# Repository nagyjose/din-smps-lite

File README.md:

# DIN-Rail Switched-Mode Power Supply Lite (`din-smps-lite`)

> Ultra-compact, cost- and space-optimized offline flyback auxiliary power supply for 35 mm DIN-rail modular enclosures, delivering a regulated +12 V DC rail.

**Project Status:** `Completed / Production Ready` | **EDA Tool:** `Autodesk Eagle 9.x` | **Category:** `Power Electronics / Hardware`

---

## 1. Overview and Purpose

The `din-smps-lite` repository provides an ultra-compact, high-efficiency offline AC/DC switched-mode power supply designed for DIN-rail distribution enclosures and localized automation sub-racks. It serves as a streamlined, space-optimized alternative to the dual-output [din-smps](https://github.com/nagyjose/din-smps) main model.

By focusing on a single high-integrity **+12 V DC** regulated rail and utilizing standing component footprints, this design achieves a minimal PCB footprint while retaining full galvanic isolation (> 3 kV) and mains protection.

### Key Features
- **Galvanic Isolation:** High-voltage isolation exceeding 3 kV via an optocoupler feedback loop and specialized flyback transformer.
- **High Efficiency & Low Standby:** Powered by the **Power Integrations TNY267PN** TinySwitch-II offline switcher with EcoSmart® technology, providing auto-restart, cycle skipping, and thermal shutdown.
- **Input Protection:** AC mains surge suppression via a Metal Oxide Varistor (`VAR1`, 420V AC / 680V clamping) and overcurrent protection via a resettable PTC fuse (`FX1`).
- **Single Regulated +12 V DC Rail:** Regulated by an **STMicroelectronics L7812ABV** linear regulator with bulk electrolytic and ceramic decoupling for noise-free relay, actuator, and bus power.
- **Space-Saving Footprints:** Utilizes vertical/standing component geometries (`_STOJ`) for axial resistors to minimize overall PCB dimensions.
- **Ready for Manufacture:** Complete Autodesk Eagle schematic (`.sch`), 2-layer PCB layout (`.brd`), CAM drill configuration (`DRILEGEND.CFG`), and PDF drawings.

---

## 2. Technical Specifications

| Parameter | Specification (`SMPS-DIN-LITE`) |
| :--- | :--- |
| **Input Voltage Range** | 85 – 265 V AC, 50/60 Hz |
| **Input Connector** | 2-position 5.00 mm screw terminal (`CON1`: Line, Neutral) |
| **Primary Topology** | Discontinuous Conduction Mode (DCM) Flyback Converter |
| **Primary Controller IC** | Power Integrations TNY267PN (DIP-8B) |
| **Flyback Transformer** | Myrra 74080 (designed for TinySwitch-II) |
| **Output Voltage** | **+12 V DC** (Regulated) |
| **Linear Post-Regulator** | STMicroelectronics L7812ABV (TO-220) |
| **Output Rectifier** | 1N5822 (3 A / 40 V Schottky Barrier Rectifier) |
| **Feedback Loop** | Sharp PC817 optocoupler + 15 V Zener diode reference |
| **Input Protection** | Resettable PTC Fuse (`FX1`) + MOV 680 V (`VAR1`, HEL-7D681K) |
| **Output Connector** | 2-position 5.00 mm screw terminal (`CON2`: +12 V, GND) |
| **PCB Form Factor** | Double-sided 1.6 mm FR4, compact DIN-rail layout |

---

## 3. Architecture & Functional Blocks

```mermaid
flowchart TD
    subgraph AC_Input["Mains AC Input Stage"]
        AC["230V AC Mains (L, N)"] --> PROT["Protection<br/>(PTC Fuse FX1 + MOV HEL-7D681K)"]
        PROT --> RECT["Full-Bridge Rectifier<br/>(4x 1N4005)"]
        RECT --> DC_BUS["DC Bus & Filter<br/>(Pi-Filter: 2x 3.3µF / 400V + 2.2mH L1)"]
    end

    subgraph Primary_Flyback["Galvanically Isolated Flyback Converter"]
        DC_BUS --> TR["Flyback Transformer<br/>(Myrra 74080)"]
        DC_BUS --> RCD["RCD Snubber<br/>(1N4005 + 2MΩ / 100kΩ + 2.2nF)"]
        RCD --> TR
        TR <--> TNY["Flyback Switcher IC<br/>(Power Integrations TNY267PN)"]
    end

    subgraph Secondary_Output["Secondary Rectification & Regulation"]
        TR --> SCHOTTKY["Secondary Rectifier<br/>(1N5822 Schottky 3A)"]
        SCHOTTKY --> SEC_FILT["Bulk Filtering<br/>(1000µF + 10µH L2 + 470µF)"]
        SEC_FILT --> REG12["Linear Regulator 12V<br/>(ST L7812ABV)"]
        REG12 --> OUT12["+12V DC Output (CON2)"]
    end

    subgraph Feedback_Loop["Optocoupler Feedback"]
        SEC_FILT --> ZENER["Voltage Reference<br/>(15V Zener D7 + R5 680Ω)"]
        ZENER --> OPTO["Galvanic Optocoupler<br/>(Sharp PC817)"]
        OPTO -.->|Isolated Feedback Current| TNY
    end

    style AC fill:#e1f5fe,stroke:#0288d1,stroke-width:1.5px
    style TNY fill:#fff3e0,stroke:#f57c00,stroke-width:2px
    style TR fill:#ede7f6,stroke:#512da8,stroke-width:2px
    style OUT12 fill:#e8f5e9,stroke:#388e3c,stroke-width:2px
```

### Circuit Operation
1. **Mains Ingress & Rectification:** AC mains enters through 2-pin terminal block `CON1`, protected against short circuits by PTC fuse `FX1` and voltage surges by varistor `VAR1`. A 1N4005 diode bridge (`D1`–`D4`) rectifies the input into a high-voltage DC bus smoothed by a pi-filter (`C1`, `C2` 3.3 µF / 400 V and `L1` 2.2 mH choke).
2. **Flyback Switching (TNY267PN):** The integrated 700 V MOSFET in `IC1` switches the primary winding of transformer `TR1` (Myrra 74080). Drain voltage transients are suppressed by the snubber network (`D5`, `R2`, `R3`, `C4`).
3. **Optocoupler Regulation:** Output voltage is sampled through a 15 V Zener diode (`D7`) driving the infrared LED of optocoupler `IC2` (PC817). The phototransistor modulates the `EN/UV` terminal of the TNY267PN, enabling cycle-skipping regulation.
4. **Secondary Smoothing & Linear Regulation:** High-efficiency rectification is handled by Schottky diode `D6` (1N5822) followed by a CLC smoothing stage (`C8`, `L2`, `C10`). Linear regulator `IC3` (L7812ABV) clamps and stabilizes the final rail at exactly **+12.0 V DC** on `CON2`.

---

## 4. Hardware Schematic & Visuals

Below is the complete schematic diagram of the compact SMPS-DIN-LITE converter:

📄 [Open original full-resolution schematic (PDF)](SMPS-DIN-LITE.pdf)

---

## 5. Repository Structure

```text
.
├── SMPS-DIN-LITE.sch              # Schematic diagram (Autodesk Eagle)
├── SMPS-DIN-LITE.brd              # 2-layer PCB layout (Autodesk Eagle)
├── SMPS-DIN-LITE.pdf              # Schematic preview drawing (PDF)
├── DRILEGEND.CFG                  # Eagle drill legend configuration
├── docs/
│   └── images/                    # Rendered 180 DPI hardware visuals
│       └── smps_din_lite_schematic.png # Schematic preview image
└── README.md                      # Main repository documentation
```

---

## 6. Bill of Materials & Core Components

| Designator | Component / Part Number | Manufacturer | Package / Footprint | Description |
| :--- | :--- | :--- | :--- | :--- |
| `IC1` | **TNY267PN** | Power Integrations | DIP-8B | TinySwitch-II offline flyback switcher IC |
| `IC2` | **PC817X4NSZ1B** | Sharp | DIP-4 | Galvanic isolation optocoupler |
| `IC3` | **L7812ABV** | STMicroelectronics | TO-220 | Linear positive voltage regulator (+12 V, 1 A) |
| `TR1` | **74080** | Myrra | PCB Mount | Flyback transformer (optimized for TNY series) |
| `D1–D4, D5` | **1N4005** | Diotec | DO-41 (Vertical) | 600 V / 1 A silicon rectifiers |
| `D6` | **1N5822** | STMicroelectronics | DO-201AD | 40 V / 3 A Schottky barrier rectifier diode |
| `D7` | **BZX55C15** | Vishay / CDIL | DO-35 (Vertical) | 15 V / 0.5 W Zener voltage reference diode |
| `VAR1` | **HEL-7D681K** | SR Passives | Radial Disk 7 mm | Metal Oxide Varistor (420 V AC continuous) |
| `FX1` | **FX100-30** | ECE | Radial | Resettable PTC fuse |
| `L1` | **COIL1010-2.2** | Ferrocore | Radial Choke | 2.2 mH power inductor (input Pi-filter) |
| `L2` | **COIL0608-0.01** | Ferrocore | Radial Choke | 10 µH power inductor (secondary filter) |
| `C1, C2` | **ECA2GM3R3B** | Panasonic | Radial Ø10 mm | 3.3 µF / 400 V DC electrolytic capacitor |
| `C8` | **EWH1EK102G20OT** | Aishi | Radial Ø10 mm | 1000 µF / 25 V low-ESR electrolytic capacitor |
| `C10` | **PF1V471MNN1020** | Elite | Radial Ø10 mm | 470 µF / 35 V low-ESR electrolytic capacitor |
| `CON1, CON2` | **XY301V-2P+ (5.00)** | Xinya | 5.00 mm Pitch | 2-position screw terminal blocks |

---

## 7. Manufacturing & EDA Guidelines

### Opening and Editing in Autodesk Eagle
1. Open Autodesk Eagle (version 8.x, 9.x, or Autodesk Fusion 360 Electronics).
2. Open project: `SMPS-DIN-LITE.sch` and `SMPS-DIN-LITE.brd`.
3. To generate Gerber / drill files for PCB production, load standard 2-layer CAM job and apply `DRILEGEND.CFG`.

### Safety and High-Voltage Notice
> [!WARNING]
> This circuit is directly connected to hazardous 230 V AC mains voltage! High voltages up to ~400 V DC are present across `C1`, `C2`, and the primary side of `TR1` during operation and for some time after disconnection.
> - Ensure appropriate creepage and clearance distances (> 6.0 mm) between primary and secondary copper traces.
> - Always bench-test using an isolating transformer and current-limited mains supply.
> - Install within a certified insulating DIN enclosure before connecting to mains.

---

## 8. Cross-Project Relationships & Ecosystem

This project is an integral building block of the **Smart Home DIN-Rail Ecosystem**:
- **[din-smps](https://github.com/nagyjose/din-smps):** Full-featured dual-output (+12 V & +5 V) DIN-rail SMPS with complete calculations and component datasheets.
- **[din-control-module](https://github.com/nagyjose/din-control-module):** Main DIN-rail central automation unit.
- **[din-relay-module](https://github.com/nagyjose/din-relay-module):** DIN-rail 8-channel power relay actuator module, powered by the +12 V rail.
- **[domovni-rozvadec-dokumentace](https://github.com/nagyjose/domovni-rozvadec-dokumentace):** Cabinet wiring diagrams and schematics showing DIN-rail modular power supplies.

---

## 9. License

This hardware project is open source and licensed under the [MIT License](LICENSE) (or CERN Open Hardware Licence v2 - Permissive).

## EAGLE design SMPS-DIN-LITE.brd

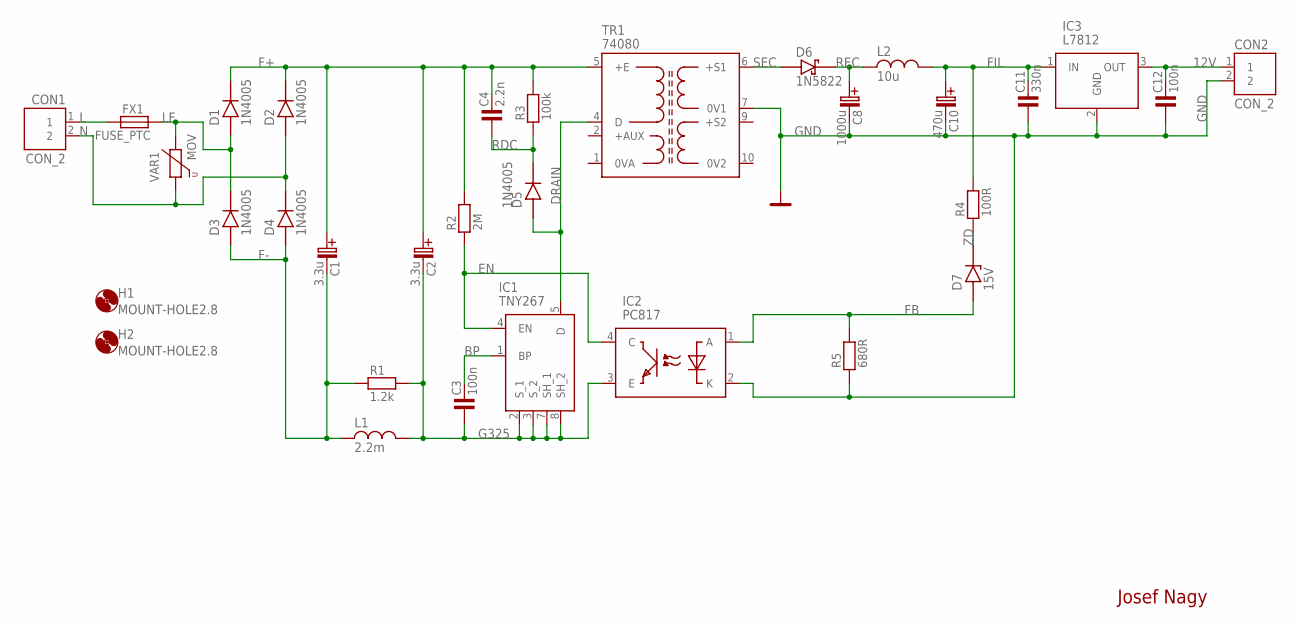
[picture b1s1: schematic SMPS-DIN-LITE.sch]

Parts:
C1, C2: 3.3u; C-EL_5
C3, C12: 100n; C-2,5
C4: 2.2n; C-10
C8: 1000u; C-EL_5
C10: 470u; C-EL_5
C11: 330n; C-5
CON1, CON2: CON_2; CON2
D1, D2, D3, D4, D5: 1N4005; DO41_V
D6: 1N5822; DO201_V
D7: 15V; DO35_V
FX1: FUSE_PTC
H1, H2: MOUNT-HOLE2.8; 2,8
IC1: TNY267; P-PACKAGE(DIP-8B)_1
IC2: PC817; DIP762W60P254L460H455Q4N
IC3: L7812; TO255P460X1020X2008-3P
L1: 2.2m; L-5
L2: 10u; L-3
R1: 1.2k; R-STOJ
R2: 2M; R-STOJ2
R3: 100k; R-STOJ
R4: 100R; R-STOJ
R5: 680R; R-STOJ
TR1: 74080
VAR1: MOV; MOV_VARISTOR

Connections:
12V: C12.2, CON2.1, IC3.3 (OUT)
BP: C3.2, IC1.1 (BP)
DRAIN: D5.A, IC1.5 (D), TR1.4 (D)
EN: IC1.4 (EN), IC2.4 (C), R2.1
F+: C1.C+ (C_EL+), C2.C+ (C_EL+), C4.2, D1.K (C), D2.K (C), R2.2, R3.2, TR1.5 (+E)
F-: C1.C- (C_EL-), D3.A, D4.A, L1.1, R1.1
FB: D7.A, IC2.1 (A), R5.2
FIL: C10.C+ (C_EL+), C11.2, IC3.1 (IN), L2.2, R4.2
G325: C2.C- (C_EL-), C3.1, IC1.2 (S_1), IC1.3 (S_2), IC1.7 (SH_1), IC1.8 (SH_2), IC2.3 (E), L1.2, R1.2
GND: C8.C- (C_EL-), C10.C- (C_EL-), C11.1, C12.1, CON2.2, IC2.2 (K), IC3.2 (GND), R5.1, TR1.7 (0V1)
L: CON1.1, FX1.1
LF: D1.A, D3.K (C), FX1.2, VAR1.2
N: CON1.2, D2.A, D4.K (C), VAR1.1
RDC: C4.1, D5.K (C), R3.1
REC: C8.C+ (C_EL+), D6.K (C), L2.1
SEC: D6.A, TR1.6 (+S1)
ZD: D7.K (C), R4.1

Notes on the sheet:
Josef Nagy

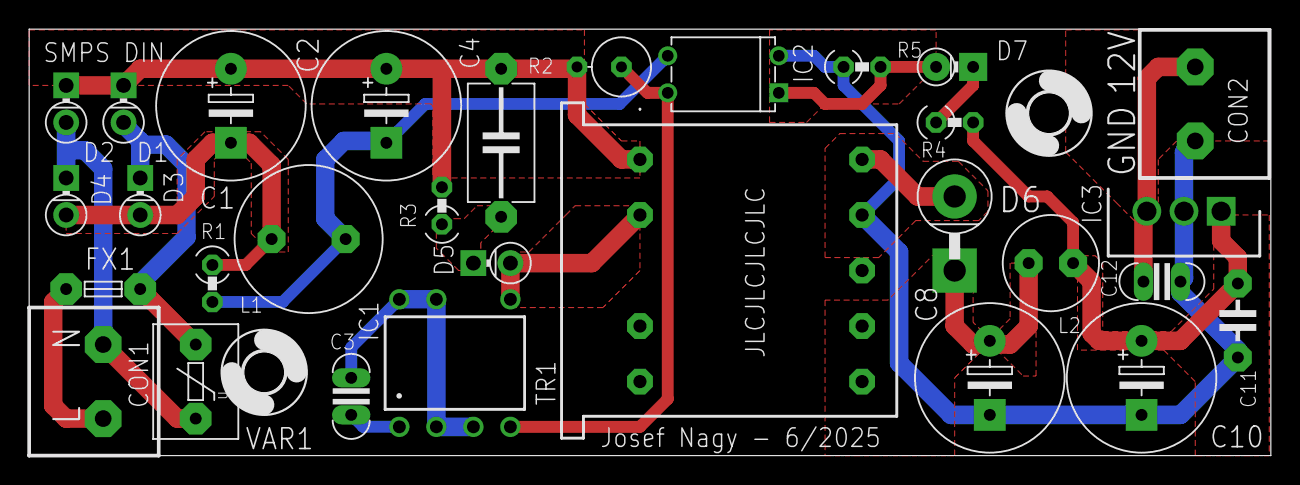
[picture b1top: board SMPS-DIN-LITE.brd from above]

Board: 2 copper layers, 85.2 x 29.3 mm, 32 parts (0 on the bottom side), 17 nets.
